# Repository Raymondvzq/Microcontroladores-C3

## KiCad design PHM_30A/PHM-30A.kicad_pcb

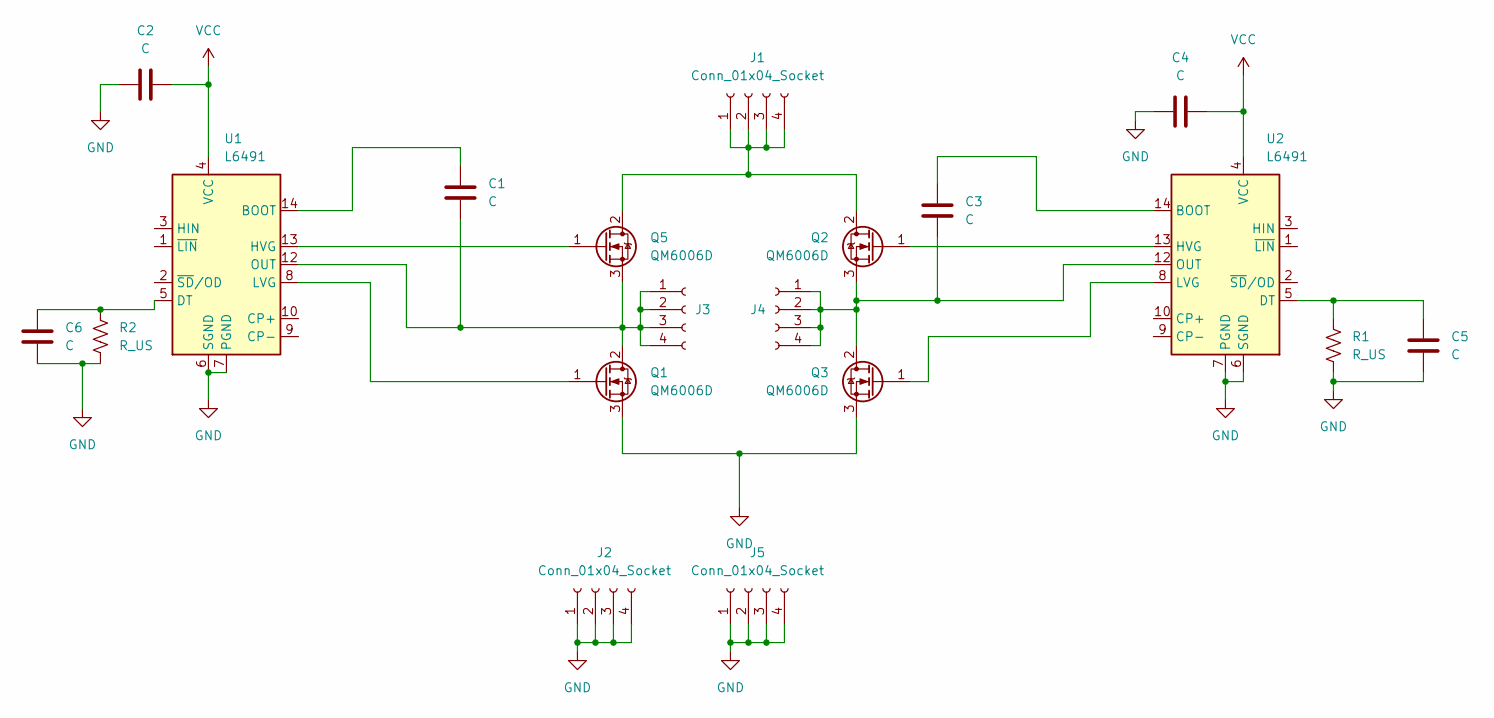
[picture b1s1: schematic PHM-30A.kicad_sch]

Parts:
C1, C2, C3, C4: C; C_0805_2012Metric
C5, C6: C; C_0603_1608Metric
J1, J2, J3, J4, J5: Conn_01x04_Socket; Connector_Castellated_1x04
Q1, Q2, Q3, Q5: QM6006D; TO-252-2
R1, R2: R_US; R_0603_1608Metric
U1, U2: L6491; SO-14_3.9x8.65mm_P1.27mm

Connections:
GND: C2.2, C4.1, C5.1, C6.1, J2.1, J2.2, J2.3, J2.4, J5.1, J5.2, J5.3, J5.4, Q1.3 (S), Q3.3 (S), R1.2, R2.2, U1.6 (SGND), U1.7 (PGND), U2.6 (SGND), U2.7 (PGND)
unnamed: J1.1, J1.2, J1.3, J1.4, Q2.2 (D), Q5.2 (D)
unnamed: C1.2, J3.1, J3.2, J3.3, J3.4, Q1.2 (D), Q5.3 (S), U1.12 (OUT)
unnamed: C3.2, J4.1, J4.2, J4.3, J4.4, Q2.3 (S), Q3.2 (D), U2.12 (OUT)
unnamed: Q1.1 (G), U1.8 (LVG)
unnamed: Q2.1 (G), U2.13 (HVG)
unnamed: Q3.1 (G), U2.8 (LVG)
unnamed: Q5.1 (G), U1.13 (HVG)
unnamed: C1.1, U1.14 (BOOT)
unnamed: C6.2, R2.1, U1.5 (DT)
unnamed: C3.1, U2.14 (BOOT)
unnamed: C5.2, R1.1, U2.5 (DT)
VCC: C2.1, C4.2, U1.4 (VCC), U2.4 (VCC)

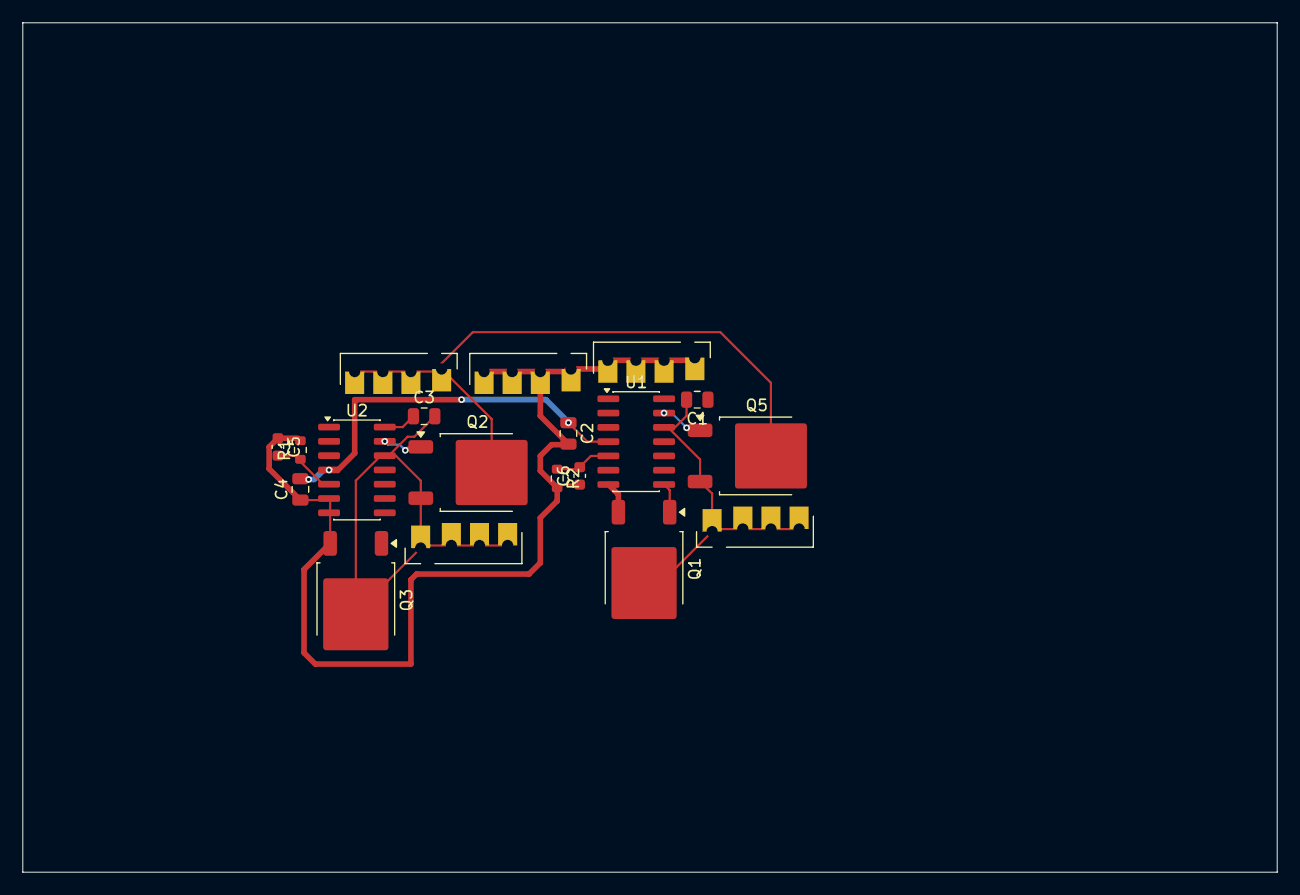
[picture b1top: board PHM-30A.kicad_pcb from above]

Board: 2 copper layers, 111.5 x 75.5 mm, 19 parts (0 on the bottom side), 13 nets.

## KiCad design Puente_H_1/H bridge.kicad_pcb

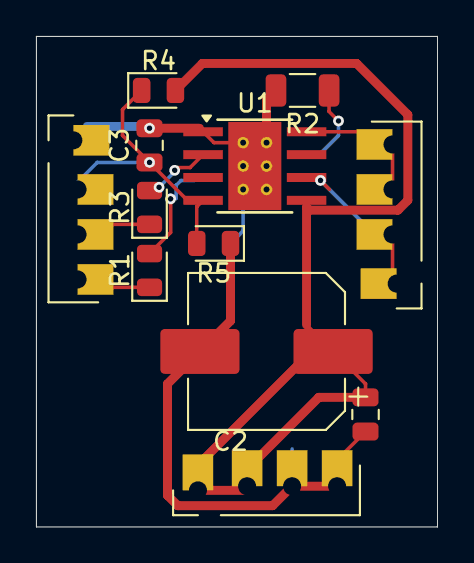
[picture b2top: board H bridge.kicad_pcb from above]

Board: 2 copper layers, 22.3 x 27.2 mm, 12 parts (0 on the bottom side), 10 nets.

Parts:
C1, C3: C; C_0805_2012Metric
C2: C_Polarized; CP_Elec_8x10.5
J1, J2, J3: Conn_01x04_Socket; Connector_Castellated_1x04
R1, R3, R4, R5: R_US; LED_0805_2012Metric
R2: R_US; C_1206_3216Metric
U1: DRV8870DDA; Texas_HTSOP-8-1EP_3.9x4.9mm_P1.27mm_EP2.95x4.9mm_Mask2.4x3.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

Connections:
/I1: R1.2, U1.3 (IN1)
/I2: R3.2, U1.2 (IN2)
/M1: J1.1, J1.2, U1.6 (OUT1)
/M2: J1.3, J1.4, U1.8 (OUT2)
GND: C1.2, C2.2, C3.2, J2.1, J3.3, J3.4, R2.2, R5.1, U1.1 (GND), U1.9 (GND)
unnamed: C3.1, J2.2, R4.1, R5.2, U1.4 (VREF)
unnamed: J2.3, R3.1
unnamed: J2.4, R1.1
unnamed: R2.1, U1.7 (ISEN)
VSS: C1.1, C2.1, J3.1, J3.2, R4.2, U1.5 (VM)

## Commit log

2025-10-09 Lito
2025-10-09 Primer intento
2025-10-09 Suspicius
2025-10-09 Create Tarea 1/
2025-10-09 Readyyyyy
2025-10-09 Nice
2025-10-09 Commit 1
2025-10-10 tar1 copy
2025-10-10 test
2025-11-17 Listo
2025-12-03 Prueba
2025-12-03 Inicializando repo después de mover carpeta
2025-12-03 Tarea 3
2025-12-03 Fix: remove broken submodules H_bridge and Puente_H_1
2025-12-03 Fix: remove submodule and restore Puente_H_1 as normal folder
2025-12-03 Easy
